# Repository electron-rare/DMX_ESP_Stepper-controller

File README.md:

# DMX_ESP_Stepper-controller

Contrôle de moteur pas à pas sur commande DMX

Contrôleur de moteur pas à pas piloté en DMX, sur ESP32 : la position et la vitesse sont commandées par deux canaux DMX distincts, avec détection d’obstacle par perte de pas.

Clément SAILLANT, pour Hémisphère — création de l’Opéra de Montpellier, 2023

clement@lelectronrare.fr

Un canal DMX est utilisé pour la commande de la position du moteur

Un autre canal DMX est utilisé pour la commande de la vitesse du moteur

Une fonction affine est utilisée pour convertir la valeur DMX en position ou vitesse

La position et la vitesse sont stockées dans des variables globales

Une fonction est utilisée pour la sécurité si un obstacle est détecté par la perte de pas du moteur

moteur : 34HS59-6004D-E1000

Angle de pas: 1.8 deg

Résolution de l'encodeur: 1000PPR(4000CPR)

https://www.omc-stepperonline.com/download/34HS59-6004D-E1000_Torque_Curve.pdf
https://www.omc-stepperonline.com/download/34HS59-6004D-E1000.pdf

Controleur CL86T V4.0

https://www.omc-stepperonline.com/index.php?route=product/product/get_file&file=389/CL86T%20(V4.0).pdf

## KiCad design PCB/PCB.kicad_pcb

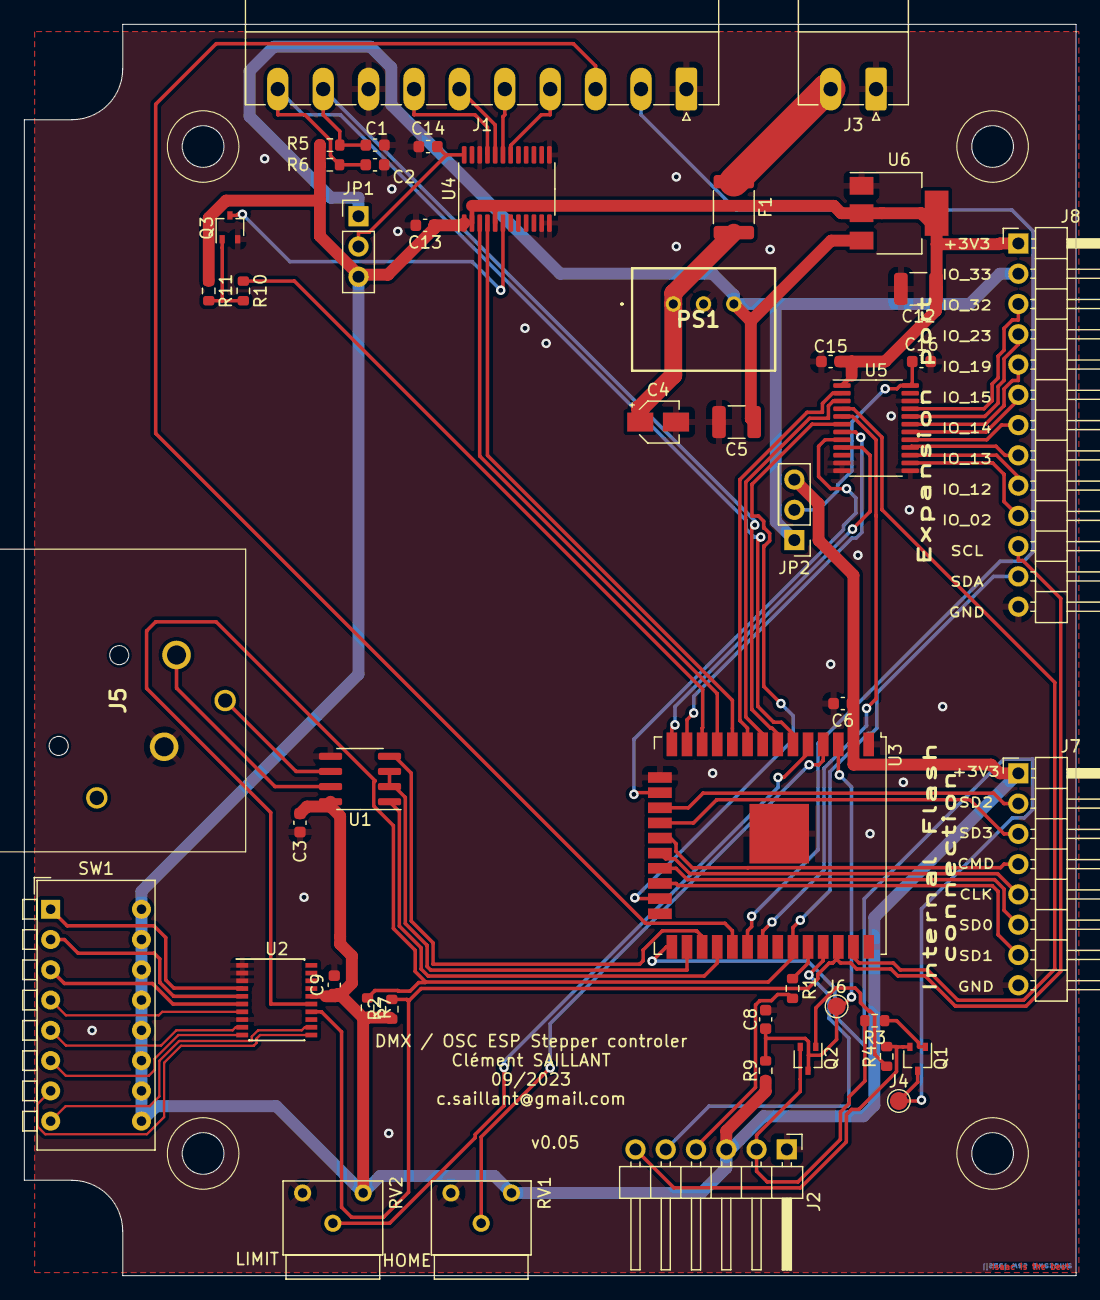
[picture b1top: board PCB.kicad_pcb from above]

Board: 2 copper layers, 88.2 x 105.0 mm, 47 parts (0 on the bottom side), 68 nets.

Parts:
C1, C2: 100nF; C_0603_1608Metric
C3, C6, C9, C13, C14, C15, C16: 0.1uF; C_0603_1608Metric
C4: 10uF/100V; CP_Elec_3x5.3
C5, C12: 10uF/100V; C_1210_3225Metric
C8: 1uF; C_0603_1608Metric
F1: 0.5A/100V; Fuse_1812_4532Metric
J1: Conn_01x10_Socket; PhoenixContact_MC_1,5_10-G-3.81_1x10_P3.81mm_Horizontal
J2: Conn_01x06; PinHeader_1x06_P2.54mm_Horizontal
J3: Screw_Terminal_01x02; PhoenixContact_MC_1,5_2-G-3.81_1x02_P3.81mm_Horizontal
J4, J6: TEST_1P; TestPoint_Pad_D1.5mm
J5: DMX-IN; AC3FAHL2-AU-PRE
J7: Conn_01x08; PinHeader_1x08_P2.54mm_Horizontal
J8: Conn_01x13; PinHeader_1x13_P2.54mm_Horizontal
JP1, JP2: Jumper_3_Open; PinHeader_1x03_P2.54mm_Vertical
PS1: TSR 0.6-4850WI; TSR0648120WI
Q1, Q2, Q3: BC847W; SOT-323_SC-70
R1, R10: 1k; R_0603_1608Metric
R2, R7: 4.7k; R_0603_1608Metric
R3, R4, R5, R6, R9, R11: 10k; R_0603_1608Metric
RV1, RV2: R_Potentiometer; Potentiometer_Bourns_3339W_Horizontal
SW1: SW_DIP_x08; SW_DIP_SPSTx08_Piano_CTS_Series194-8MSTN_W7.62mm_P2.54mm
U1: SP3485CN; SOIC-8_3.9x4.9mm_P1.27mm
U2: PCF8574; SSOP-20_4.4x6.5mm_P0.65mm
U3: ESP32-WROOM; ESP32-WROOM-32U
U4, U5: 74LVX3245TTR; TSSOP-24_4.4x7.8mm_P0.65mm
U6: AMS1117-3.3; SOT-223-3_TabPin2

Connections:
+3V3: C3.1, C6.1, C9.1, C12.1, C13.1, C15.1, J2.3, J7.1, J8.1, JP1.3 (B), JP2.3 (B), R2.1, R5.2, R6.2, R7.2, R9.2, R11.1, RV1.1, RV2.1, SW1.9, SW1.10, SW1.11, SW1.12, SW1.13, SW1.14, SW1.15, SW1.16, U1.8 (VCC), U2.16 (VDD), U3.2 (VCC), U4.1 (VCCA), U4.2 (DIR), U4.5 (A3), U5.1 (VCCA), U6.2 (VO)
+5V: C5.1, J8.2, JP1.1 (A), JP2.1 (A), PS1.3 (+VOUT), U6.3 (VI)
/CLK: J7.5, U3.20 (CLK/IO6)
/CMD: J7.4, U3.19 (CMD/IO11)
/DIR+: U3.10 (IO25), U4.4 (A2)
/DMX/XLR_DMX_2: J5.2, U1.7 (B)
/DMX/XLR_DMX_3: J5.3, U1.6 (A)
/DMX_DE: U1.2 (~RE), U1.3 (DE), U3.26 (IO4)
/DMX_DI: U1.4 (DI), U3.27 (IO16)
/DMX_RO: U1.1 (RO), U3.28 (IO17)
/EA+: J1.3, U3.29 (IO5)
/EB+: J1.2, U3.30 (IO18)
/ENA: R10.1, U3.12 (IO27)
/ENA-: Q3.3 (C), U4.6 (A4)
/END_POT: RV2.2, U3.5 (SENSOR_VN)
/END_SWITCH: C1.1, J1.9, R5.1, U3.7 (IO35)
/ESP32_BOOT: J4.1, Q1.3 (C), U3.25 (IO0)
/ESP32_EN: C8.1, J6.1, Q2.3 (C), R9.1, U3.3 (EN)
/ESP32_RXI: R1.1, U3.34 (RXD0)
/ESP32_TXO: J2.5, U3.35 (TXD0)
/IO12: U3.14 (IO12), U5.9 (A7)
/IO13: U3.16 (IO13), U5.8 (A6)
/IO14: U3.13 (IO14), U5.7 (A5)
/IO15: U3.23 (IO15), U5.6 (A4)
/IO19: U3.31 (IO19), U5.5 (A3)
/IO23: U3.37 (IO23), U5.4 (A2)
/IO32_One-wire: U3.8 (IO32), U5.3 (A1)
/IO33: U3.9 (IO33), U5.2 (DIR)
/PROG_DTR: J2.6, Q1.2 (E), R4.2
/PROG_RTS: J2.2, Q2.2 (E), R3.2
/PUL+: U3.11 (IO26), U4.3 (A1)
/SCL: J8.11, R2.2, U2.14 (SCL), U3.36 (IO22)
/SD0: J7.6, U3.21 (SD0/IO7)
/SD1: J7.7, U3.22 (SD1/IO8)
/SD2: J7.2, U3.17 (SD2/IO9)
/SD3: J7.3, U3.18 (SD3/IO10)
/SDA: J8.12, R7.1, U2.15 (SDA), U3.33 (IO21)
/START_POT: RV1.2, U3.4 (SENSOR_VP)
/START_SWITCH: C2.1, J1.10, R6.1, U3.6 (IO34)
/Shifter level1/B1: J8.3, U5.21 (B1)
/Shifter level1/B2: J8.4, U5.20 (B2)
/Shifter level1/B3: J8.5, U5.19 (B3)
/Shifter level1/B4: J8.6, U5.18 (B4)
/Shifter level1/B5: J8.7, U5.17 (B5)
/Shifter level1/B6: J8.8, U5.16 (B6)
/Shifter level1/B7: J8.9, U5.15 (B7)
/Shifter level1/B8: J8.10, U5.14 (B8)
/Shifter level stepper/B1: J1.7, U4.21 (B1)
/Shifter level stepper/B2: J1.6, U4.20 (B2)
/Shifter level stepper/B3: J1.5, U4.19 (B3)
/Shifter level stepper/B4: J1.4, U4.18 (B4)
/VDD_EXP: C16.1, JP2.2 (C), U5.24 (VCCB)
/VDD_STEPPER: C14.1, JP1.2 (C), U4.24 (VCCB)
GND: C1.2, C2.2, C3.2, C4.2, C5.2, C6.2, C8.2, C9.2, C12.2, C13.2, C14.2, C15.2, C16.2, J1.1, J1.8, J2.1, J3.1, J5.1, J7.8, J8.13, PS1.2 (GND), Q3.2 (E), RV1.3, RV2.3, U1.5 (GND), U2.1 (A0), U2.2 (A1), U2.3 (A2), U2.8 (VSS), U3.1 (GND), U3.15 (GND), U3.38 (GND), U3.39 (GND_PAD), U4.11 (GND), U4.12 (GND), U4.13 (GND), U4.22 (*G), U5.11 (GND), U5.12 (GND), U5.13 (GND), U5.22 (*G), U6.1 (GND)
unnamed: J2.4, R1.2
unnamed: F1.1, J3.2
unnamed: C4.1, F1.2, PS1.1 (+VIN)
unnamed: Q1.1 (B), R3.1
unnamed: Q2.1 (B), R4.1
unnamed: Q3.1 (B), R10.2, R11.2
unnamed: SW1.1, U2.4 (P0)
unnamed: SW1.2, U2.5 (P1)
unnamed: SW1.3, U2.6 (P2)
unnamed: SW1.4, U2.7 (P3)
unnamed: SW1.5, U2.9 (P4)
unnamed: SW1.6, U2.10 (P5)
unnamed: SW1.7, U2.11 (P6)
unnamed: SW1.8, U2.12 (P7)

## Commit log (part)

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2023-05-28 Last update
2023-05-30 update ENV
2023-09-11 update PCB
2023-09-11 update Code
2023-09-15 clean file
2023-09-15 dmx update
2023-09-15 update comment
2023-10-11 add expansion port and level shifter in progress
